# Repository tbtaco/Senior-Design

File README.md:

The Senior Design project I was able to be a part of in Fall 2019 and Spring 2020 at K-State was the "MAC Address Finder".  For that, I worked in a group of 4 to fully design and build our device.  My role was mainly designing the circuit and building the board containing the microcontroller, and the board with the Wi-Fi module.  The device is needed in the residence halls for IT staff to quickly get certain device's MAC addresses.  The main reason for needing this device is the Google Home Mini.  They normally don't have a printed MAC address on the outside of the product and must be connected to a network to retrieve the address.  Our device creates that network to connect to and gives a very easy way to see this address.  The MAC address can then be used to manually add the device to the university network.

Schematics and board layouts can be found in the [EAGLE](https://github.com/tbtaco/Senior-Design/tree/main/EAGLE) directory.  The 3 main folders in there represent the separate orders I placed.  The final versions of each board I designed are:

[Main Board](https://github.com/tbtaco/Senior-Design/tree/main/EAGLE/Batch%201/Main%20Board) - This was the first version of the main PCB and I intended on redoing it at some point but it never happened due to budget constraints, time constraints, and Covid-19's impact on everything.
    
[Wifi Board](https://github.com/tbtaco/Senior-Design/tree/main/EAGLE/Batch%203/Wifi%20Board%20Rework) - I had the Wi-Fi portion working on a breadboard for the most part and turned that into a PCB.  There were some inconsistencies with different online documentation that messed up a couple things with my first version of the Wi-Fi board PCB.  We didn't have time for several attempts so I designed some breakout boards to test things before ordering the final version of this board.  The final version has several switches for debugging just in case things went horribly wrong which could easily be removed if another version were possibe.
    
[Button Board](https://github.com/tbtaco/Senior-Design/tree/main/EAGLE/Batch%201/Button%20Board) - A rather simple board that has an RGB LED and 3 buttons for input.
    
[Programmer Board](https://github.com/tbtaco/Senior-Design/tree/main/EAGLE/Batch%202/Programmer%20Board) - After several redesigns, this is the final board I created to assist with programming the microcontroller and Wi-Fi module.  It fits on top of an Arduino Uno for programming the microcontroller, and on top of a Metro M4 Express for programming the Wi-Fi module.

I also wrote the code to go on the microcontroller.  I hadn't intended on writing the final code for this project but it sort of just happened as I needed it for testing and we were short on time toward the end of semester.  This Arduino file along with the two edited programs for programming the boards can be found in the [Arduino](https://github.com/tbtaco/Senior-Design/tree/main/Arduino) directory.

I have some additional pictures and screenshots that don't fit in one of the two categories above, so I put them in the [Other Resources](https://github.com/tbtaco/Senior-Design/tree/main/Other%20Resources) directory.

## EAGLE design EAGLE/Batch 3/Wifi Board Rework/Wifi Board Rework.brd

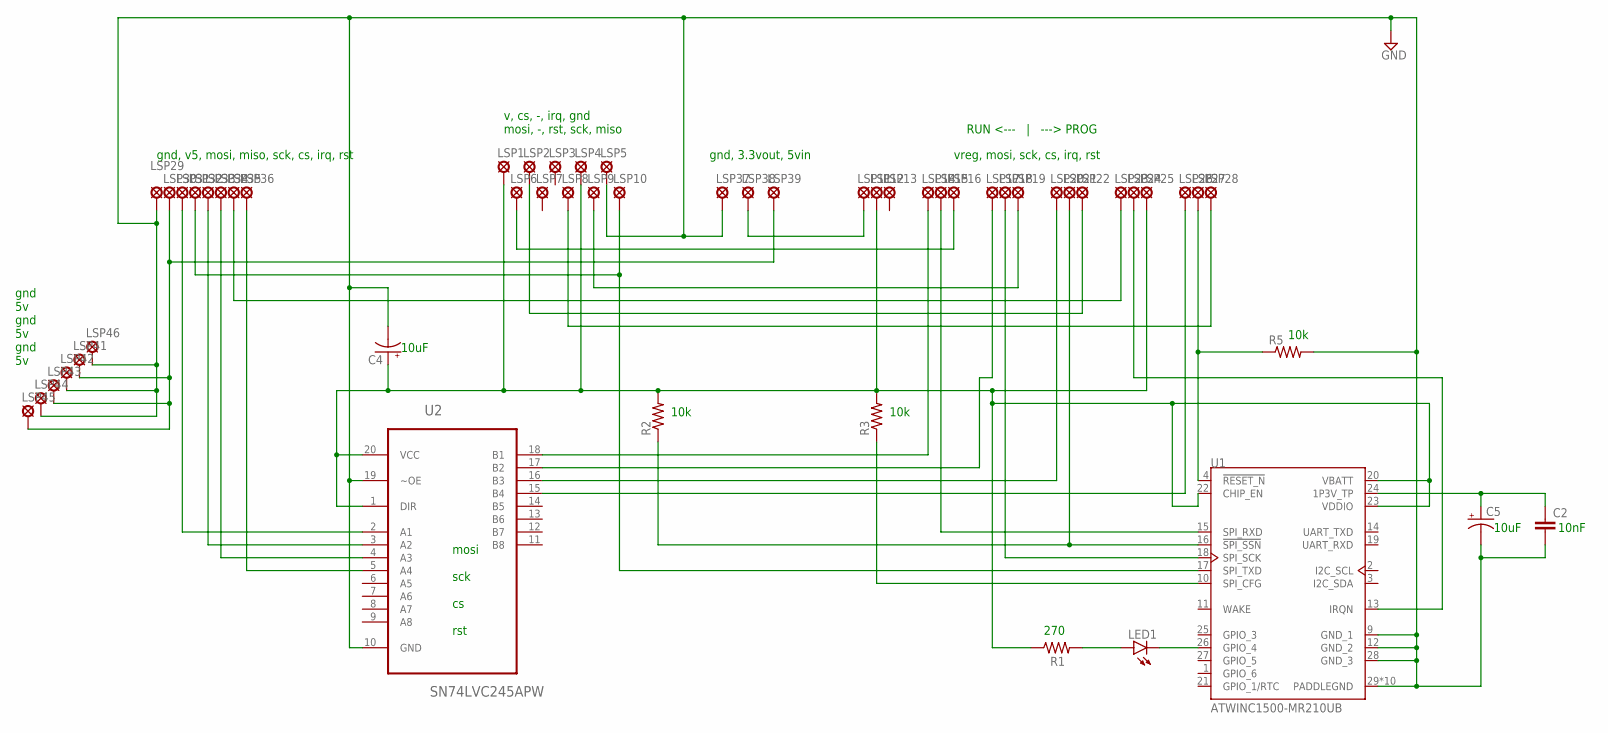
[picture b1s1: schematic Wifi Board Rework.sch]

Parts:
C2: C5/2.5; C5B2.5
C4, C5: CPOL-USE2-4; E2-4
LED1: LED5MM
LSP1, LSP2, LSP3, LSP4, LSP5, LSP7, LSP8, LSP9, LSP10, LSP11, LSP12, LSP13, LSP14, LSP15, LSP16, LSP17, LSP18, LSP19, LSP20, LSP21, LSP22, LSP23, LSP24, LSP25, LSP26, LSP27, LSP28, LSP30, LSP31, LSP32, LSP33, LSP34, LSP35, LSP36, LSP38, LSP39, LSP41, LSP42, LSP43, LSP44, LSP45: LSP10_CLSP10_C; LSP10_C
LSP6, LSP29, LSP37, LSP46: LSP10_S
R1, R2, R3, R5: R-US_VMTA55; VMTA55
U1: ATWINC1500-MR210UB; MICROCHIP_ATWINC1500-MR210UB
U2: SN74LVC245APW; SOP65P640X120-20N

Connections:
GND: C2.2, C4.-, C5.-, LSP5.P$1, LSP29.P$1, LSP37.P$1, LSP42.P$1, LSP44.P$1, LSP46.P$1, R5.2, U1.9 (GND_1), U1.12 (GND_2), U1.28 (GND_3), U1.29 (PADDLEGND), U1.P$1 (PADDLEGND), U1.P$2 (PADDLEGND), U1.P$3 (PADDLEGND), U1.P$4 (PADDLEGND), U1.P$5 (PADDLEGND), U1.P$6 (PADDLEGND), U1.P$7 (PADDLEGND), U1.P$8 (PADDLEGND), U1.P$9 (PADDLEGND), U2.10 (GND), U2.19 (~OE)
unnamed: LED1.K (C), U1.26 (GPIO_4)
unnamed: LED1.A, R1.2
unnamed: C4.+, LSP1.P$1, LSP4.P$1, LSP12.P$1, LSP25.P$1, R1.1, R2.2, R3.2, U1.20 (VBATT), U1.22 (CHIP_EN), U1.23 (VDDIO), U2.1 (DIR), U2.20 (VCC)
unnamed: LSP11.P$1, LSP38.P$1
unnamed: R3.1, U1.10 (SPI_CFG)
unnamed: LSP10.P$1, LSP32.P$1, U1.17 (SPI_TXD)
unnamed: LSP30.P$1, LSP39.P$1, LSP41.P$1, LSP43.P$1, LSP45.P$1
unnamed: LSP23.P$1, LSP35.P$1
unnamed: LSP15.P$1, U1.15 (SPI_RXD)
unnamed: LSP6.P$1, LSP16.P$1
unnamed: LSP9.P$1, LSP19.P$1
unnamed: LSP2.P$1, LSP22.P$1
unnamed: LSP24.P$1, U1.13 (IRQN)
unnamed: C2.1, C5.+, U1.24 (1P3V_TP)
unnamed: LSP14.P$1, U2.18 (B1)
unnamed: LSP17.P$1, U2.17 (B2)
unnamed: LSP20.P$1, U2.16 (B3)
unnamed: LSP26.P$1, U2.15 (B4)
unnamed: LSP27.P$1, R5.1, U1.4 (!RESET_N)
unnamed: LSP34.P$1, U2.4 (A3)
unnamed: LSP18.P$1, U1.18 (SPI_SCK)
unnamed: LSP21.P$1, R2.1, U1.16 (!SPI_SSN)
unnamed: LSP36.P$1, U2.5 (A4)
unnamed: LSP33.P$1, U2.3 (A2)
unnamed: LSP31.P$1, U2.2 (A1)
unnamed: LSP8.P$1, LSP28.P$1

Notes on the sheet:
v, cs, -, irq, gnd mosi, -, rst, sck, miso
vreg, mosi, sck, cs, irq, rst
gnd, v5, mosi, miso, sck, cs, irq, rst
10k
10uF
10nF
270
gnd, 3.3vout, 5vin
RUN <--- | ---> PROG
gnd 5v gnd 5v gnd 5v
mosi sck cs rst

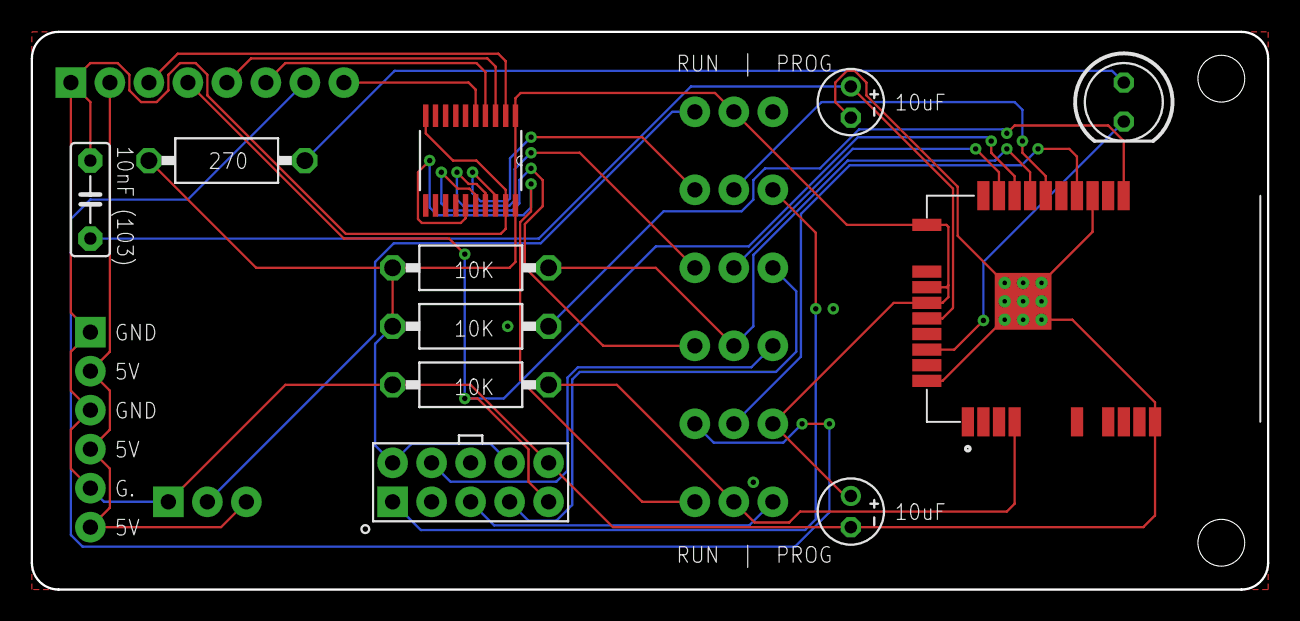
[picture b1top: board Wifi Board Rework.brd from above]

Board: 2 copper layers, 80.5 x 36.3 mm, 55 parts (0 on the bottom side), 27 nets.

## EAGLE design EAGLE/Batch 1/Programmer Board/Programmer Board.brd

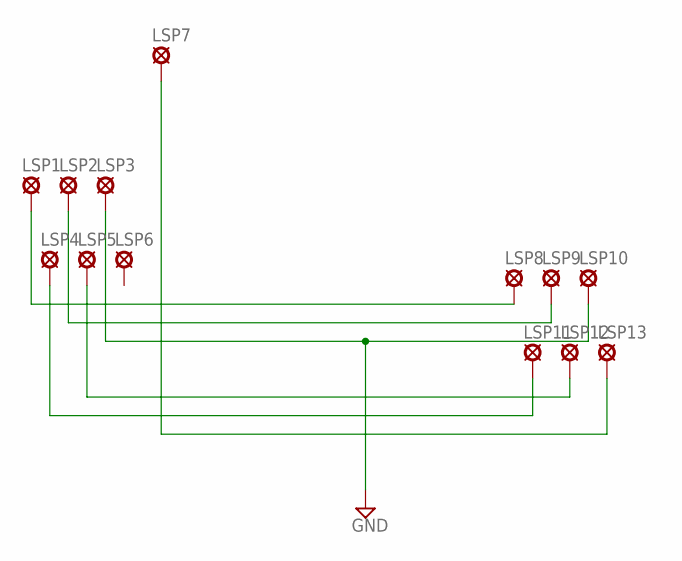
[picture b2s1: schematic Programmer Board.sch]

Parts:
LSP1, LSP2, LSP3, LSP4, LSP5, LSP6, LSP7, LSP8, LSP9, LSP10, LSP11, LSP12, LSP13: LSP10_CLSP10_C; LSP10_C

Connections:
GND: LSP3.P$1, LSP10.P$1
unnamed: LSP1.P$1, LSP8.P$1
unnamed: LSP2.P$1, LSP9.P$1
unnamed: LSP4.P$1, LSP11.P$1
unnamed: LSP5.P$1, LSP12.P$1
unnamed: LSP7.P$1, LSP13.P$1

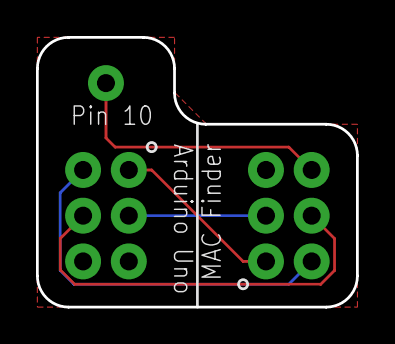
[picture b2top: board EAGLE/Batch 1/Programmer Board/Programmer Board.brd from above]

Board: 2 copper layers, 17.8 x 15.0 mm, 13 parts (0 on the bottom side), 6 nets.

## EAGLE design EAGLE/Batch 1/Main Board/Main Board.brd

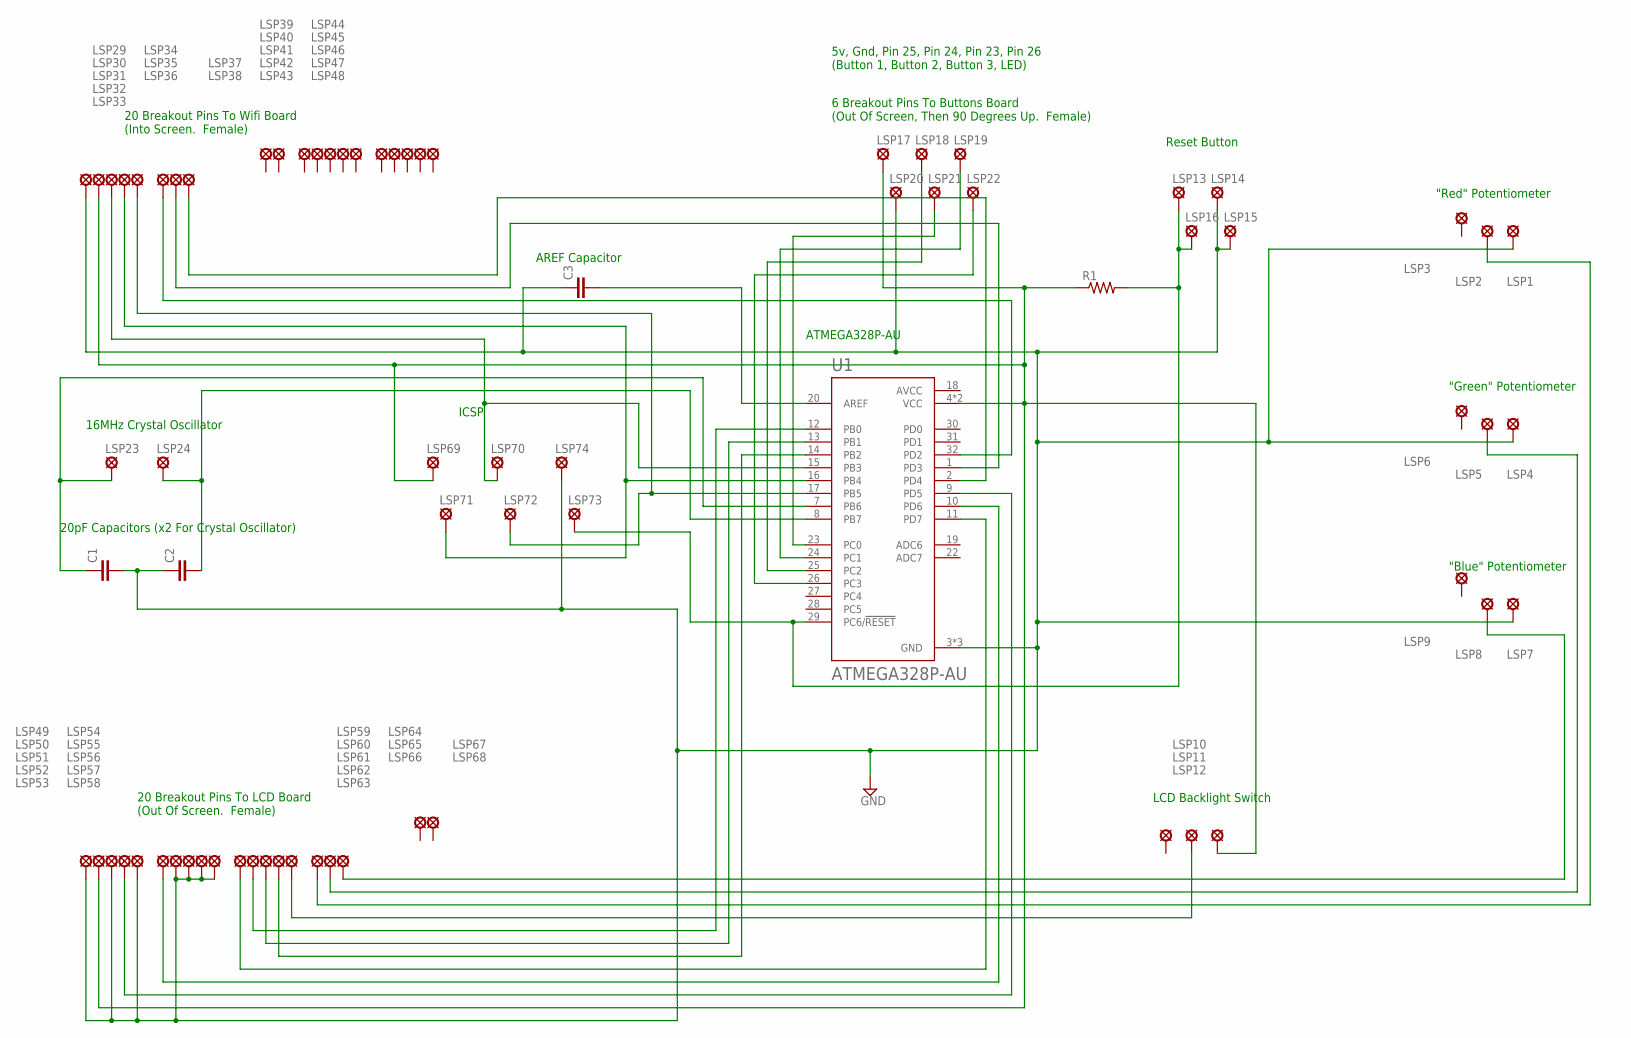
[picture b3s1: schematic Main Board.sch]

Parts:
C1, C2, C3: C5/2.5; C5B2.5
LSP1, LSP2, LSP3, LSP4, LSP5, LSP6, LSP7, LSP8, LSP9, LSP10, LSP11, LSP12, LSP13, LSP14, LSP15, LSP16, LSP17, LSP18, LSP19, LSP20, LSP21, LSP22, LSP23, LSP24, LSP29, LSP30, LSP31, LSP32, LSP33, LSP34, LSP35, LSP36, LSP37, LSP38, LSP39, LSP40, LSP41, LSP42, LSP43, LSP44, LSP45, LSP46, LSP47, LSP48, LSP49, LSP50, LSP51, LSP52, LSP53, LSP54, LSP55, LSP56, LSP57, LSP58, LSP59, LSP60, LSP61, LSP62, LSP63, LSP64, LSP65, LSP66, LSP67, LSP68, LSP69, LSP70, LSP71, LSP72, LSP73, LSP74: LSP10_CLSP10_C; LSP10_C
R1: R-US_VMTA55; VMTA55
U1: ATMEGA328P-AU; QFP80P900X900X120-32N

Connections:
AVCC: U1.18 (AVCC)
GND: C1.2, C2.1, C3.1, LSP1.P$1, LSP4.P$1, LSP7.P$1, LSP14.P$1, LSP15.P$1, LSP20.P$1, LSP29.P$1, LSP49.P$1, LSP51.P$1, LSP53.P$1, LSP55.P$1, LSP56.P$1, LSP57.P$1, LSP58.P$1, LSP74.P$1, U1.3 (GND), U1.5 (GND), U1.21 (GND)
unnamed: LSP2.P$1, LSP64.P$1
unnamed: LSP31.P$1, LSP70.P$1, U1.15 (PB3)
unnamed: LSP5.P$1, LSP65.P$1
unnamed: C1.1, LSP23.P$1, U1.7 (PB6)
unnamed: C2.2, LSP24.P$1, U1.8 (PB7)
unnamed: LSP8.P$1, LSP66.P$1
unnamed: LSP33.P$1, LSP72.P$1, U1.17 (PB5)
unnamed: LSP32.P$1, LSP71.P$1, U1.16 (PB4)
unnamed: LSP13.P$1, LSP16.P$1, LSP73.P$1, R1.2, U1.29 (PC6/!RESET)
unnamed: LSP22.P$1, U1.26 (PC3)
unnamed: LSP18.P$1, U1.25 (PC2)
unnamed: LSP19.P$1, U1.24 (PC1)
unnamed: LSP52.P$1, U1.9 (PD5)
unnamed: LSP54.P$1, U1.10 (PD6)
unnamed: LSP59.P$1, U1.11 (PD7)
unnamed: LSP60.P$1, U1.12 (PB0)
unnamed: LSP61.P$1, U1.13 (PB1)
unnamed: LSP62.P$1, U1.14 (PB2)
unnamed: LSP11.P$1, LSP63.P$1
unnamed: LSP12.P$1, LSP17.P$1, LSP30.P$1, LSP50.P$1, LSP69.P$1, R1.1, U1.4 (VCC), U1.6 (VCC)
unnamed: LSP21.P$1, U1.23 (PC0)
unnamed: C3.2, U1.20 (AREF)
unnamed: LSP34.P$1, U1.32 (PD2)
unnamed: LSP35.P$1, U1.1 (PD3)
unnamed: LSP36.P$1, U1.2 (PD4)

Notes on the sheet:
ICSP
ATMEGA328P-AU
6 Breakout Pins To Buttons Board (Out Of Screen, Then 90 Degrees Up. Female)
20 Breakout Pins To Wifi Board (Into Screen. Female)
20 Breakout Pins To LCD Board (Out Of Screen. Female)
16MHz Crystal Oscillator
20pF Capacitors (x2 For Crystal Oscillator)
Reset Button
"Red" Potentiometer
"Green" Potentiometer
"Blue" Potentiometer
LCD Backlight Switch
AREF Capacitor
5v, Gnd, Pin 25, Pin 24, Pin 23, Pin 26 (Button 1, Button 2, Button 3, LED)

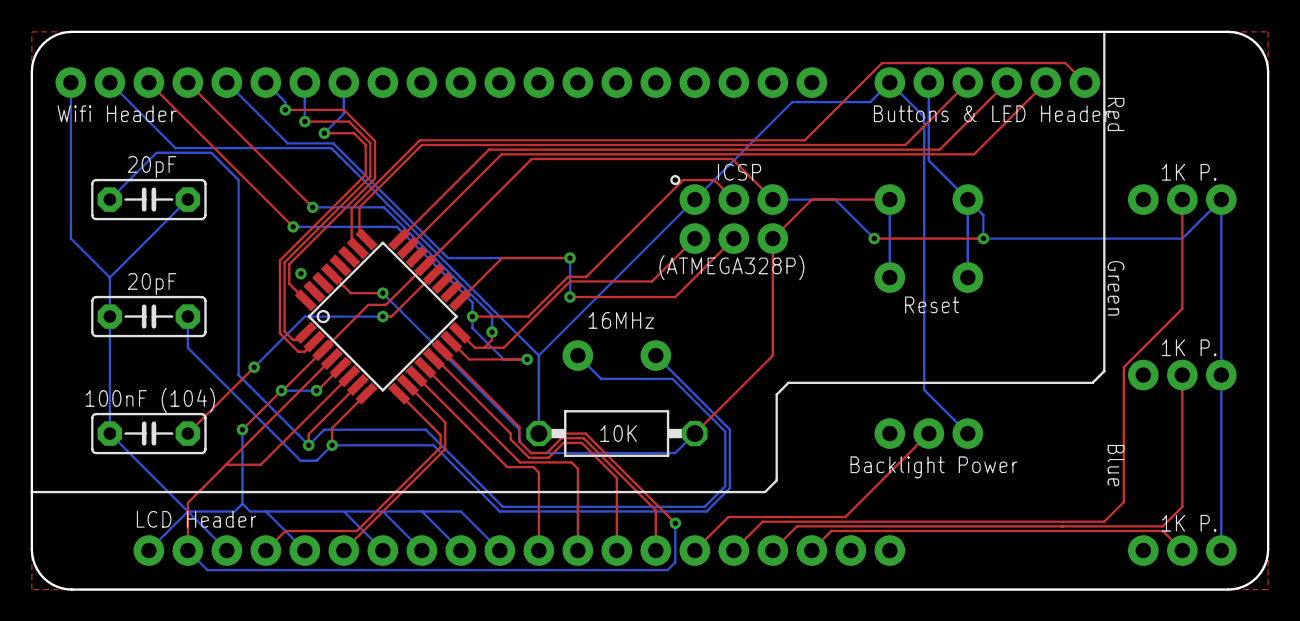
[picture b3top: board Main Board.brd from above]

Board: 2 copper layers, 80.5 x 36.3 mm, 75 parts (0 on the bottom side), 26 nets.

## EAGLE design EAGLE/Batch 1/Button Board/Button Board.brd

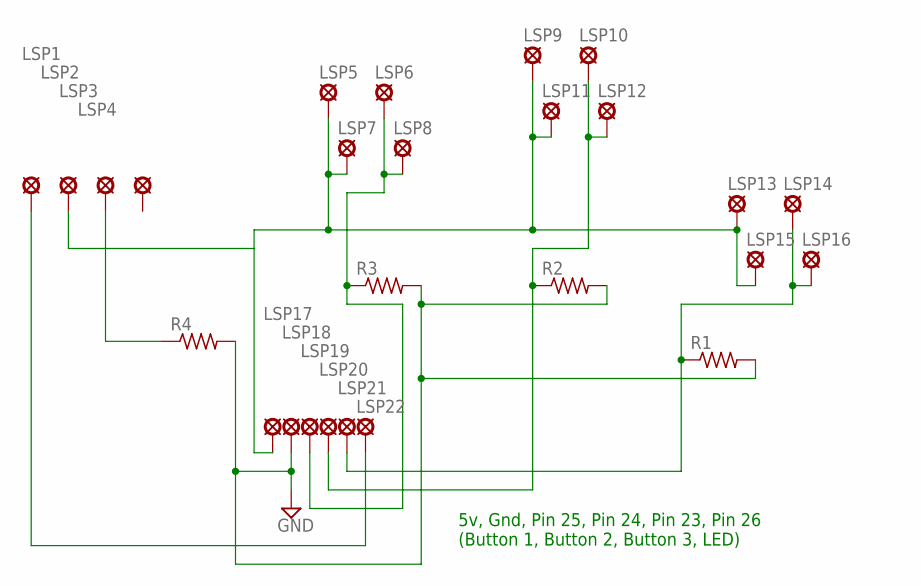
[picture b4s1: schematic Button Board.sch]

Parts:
LSP1, LSP2, LSP3, LSP4, LSP5, LSP6, LSP7, LSP8, LSP9, LSP10, LSP11, LSP12, LSP13, LSP14, LSP15, LSP16, LSP17, LSP18, LSP19, LSP20, LSP21, LSP22: LSP10_CLSP10_C; LSP10_C
R1, R2, R3, R4: R-US_VMTA55; VMTA55

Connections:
GND: LSP18.P$1, R1.2, R2.2, R3.2, R4.2
unnamed: LSP6.P$1, LSP8.P$1, LSP19.P$1, R3.1
unnamed: LSP3.P$1, R4.1
unnamed: LSP10.P$1, LSP12.P$1, LSP20.P$1, R2.1
unnamed: LSP2.P$1, LSP5.P$1, LSP7.P$1, LSP9.P$1, LSP11.P$1, LSP13.P$1, LSP15.P$1, LSP17.P$1
unnamed: LSP14.P$1, LSP16.P$1, LSP21.P$1, R1.1
unnamed: LSP1.P$1, LSP22.P$1

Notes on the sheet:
5v, Gnd, Pin 25, Pin 24, Pin 23, Pin 26 (Button 1, Button 2, Button 3, LED)

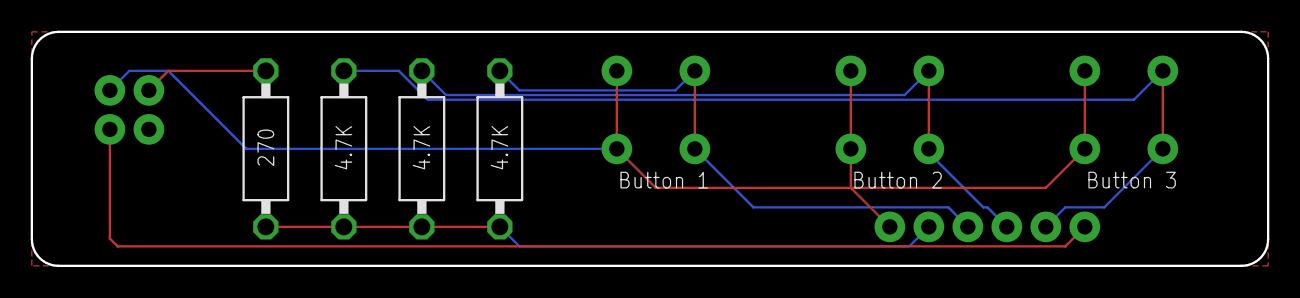
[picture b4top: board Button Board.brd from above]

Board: 2 copper layers, 80.5 x 15.2 mm, 26 parts (0 on the bottom side), 7 nets.

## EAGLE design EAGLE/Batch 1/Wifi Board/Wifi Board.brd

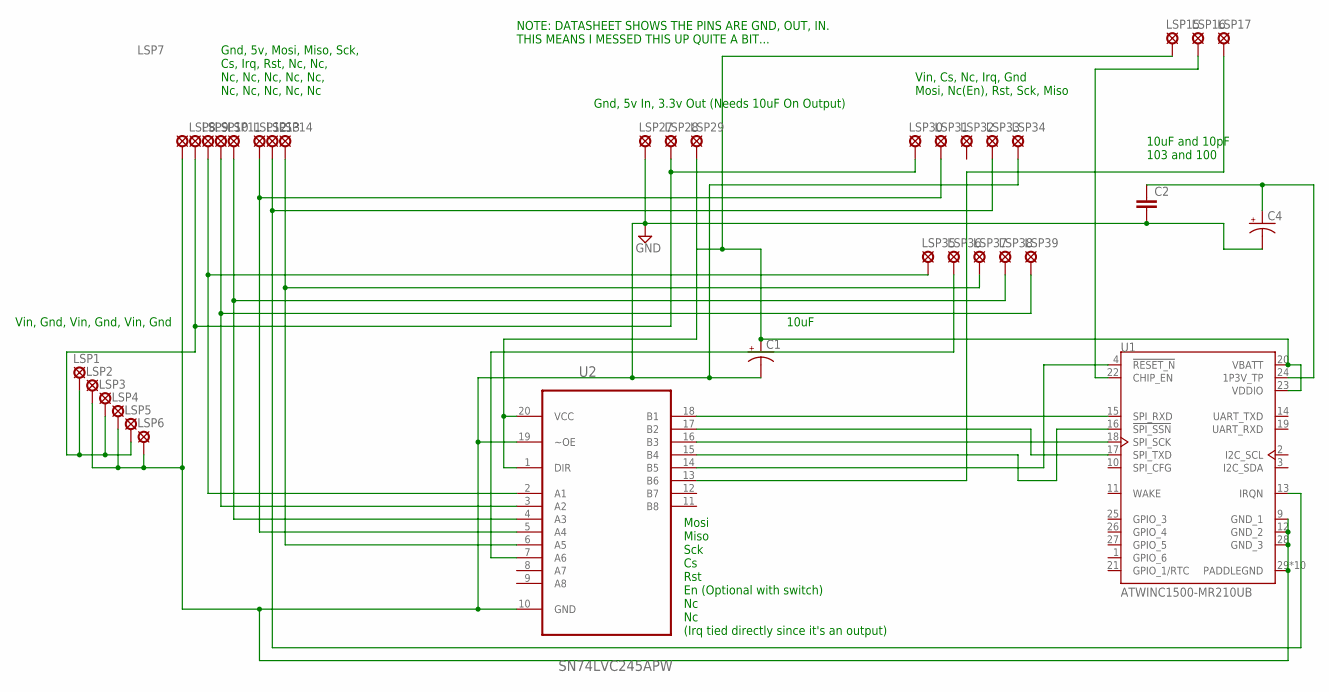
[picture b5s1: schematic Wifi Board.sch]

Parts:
C1, C4: CPOL-USE2-4; E2-4
C2: C5/2.5; C5B2.5
LSP1, LSP2, LSP3, LSP4, LSP5, LSP6, LSP7, LSP8, LSP9, LSP10, LSP11, LSP12, LSP13, LSP14, LSP15, LSP16, LSP17, LSP27, LSP28, LSP29, LSP30, LSP31, LSP32, LSP33, LSP34, LSP35, LSP36, LSP37, LSP38, LSP39: LSP10_CLSP10_C; LSP10_C
U1: ATWINC1500-MR210UB; MICROCHIP_ATWINC1500-MR210UB
U2: SN74LVC245APW; SOP65P640X120-20N

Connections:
GND: C1.-, C2.2, C4.-, LSP2.P$1, LSP4.P$1, LSP6.P$1, LSP7.P$1, LSP27.P$1, LSP34.P$1, U1.9 (GND_1), U1.12 (GND_2), U1.28 (GND_3), U1.29 (PADDLEGND), U1.P$1 (PADDLEGND), U1.P$2 (PADDLEGND), U1.P$3 (PADDLEGND), U1.P$4 (PADDLEGND), U1.P$5 (PADDLEGND), U1.P$6 (PADDLEGND), U1.P$7 (PADDLEGND), U1.P$8 (PADDLEGND), U1.P$9 (PADDLEGND), U2.10 (GND), U2.19 (~OE)
unnamed: LSP36.P$1, U2.7 (A6)
unnamed: LSP1.P$1, LSP3.P$1, LSP5.P$1, LSP8.P$1, LSP28.P$1, LSP30.P$1
unnamed: C1.+, LSP15.P$1, LSP29.P$1, U1.20 (VBATT), U1.23 (VDDIO), U2.1 (DIR), U2.20 (VCC)
unnamed: LSP9.P$1, LSP35.P$1, U2.2 (A1)
unnamed: LSP10.P$1, LSP39.P$1, U2.3 (A2)
unnamed: LSP11.P$1, LSP38.P$1, U2.4 (A3)
unnamed: LSP12.P$1, LSP31.P$1, U2.5 (A4)
unnamed: LSP13.P$1, LSP33.P$1, U1.13 (IRQN)
unnamed: LSP14.P$1, LSP37.P$1, U2.6 (A5)
unnamed: U1.15 (SPI_RXD), U2.18 (B1)
unnamed: U1.17 (SPI_TXD), U2.17 (B2)
unnamed: U1.18 (SPI_SCK), U2.16 (B3)
unnamed: U1.16 (!SPI_SSN), U2.15 (B4)
unnamed: LSP17.P$1, U2.13 (B6)
unnamed: U1.4 (!RESET_N), U2.14 (B5)
unnamed: LSP16.P$1, U1.22 (CHIP_EN)
unnamed: C2.1, C4.+, U1.24 (1P3V_TP)

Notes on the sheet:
Gnd, 5v, Mosi, Miso, Sck, Cs, Irq, Rst, Nc, Nc, Nc, Nc, Nc, Nc, Nc, Nc, Nc, Nc, Nc, Nc
Gnd, 5v In, 3.3v Out (Needs 10uF On Output)
Vin, Cs, Nc, Irq, Gnd Mosi, Nc(En), Rst, Sck, Miso
Vin, Gnd, Vin, Gnd, Vin, Gnd
10uF
Mosi Miso Sck Cs Rst En (Optional with switch) Nc Nc (Irq tied directly since it's an output)
10uF and 10pF 103 and 100
NOTE: DATASHEET SHOWS THE PINS ARE GND, OUT, IN. THIS MEANS I MESSED THIS UP QUITE A BIT...

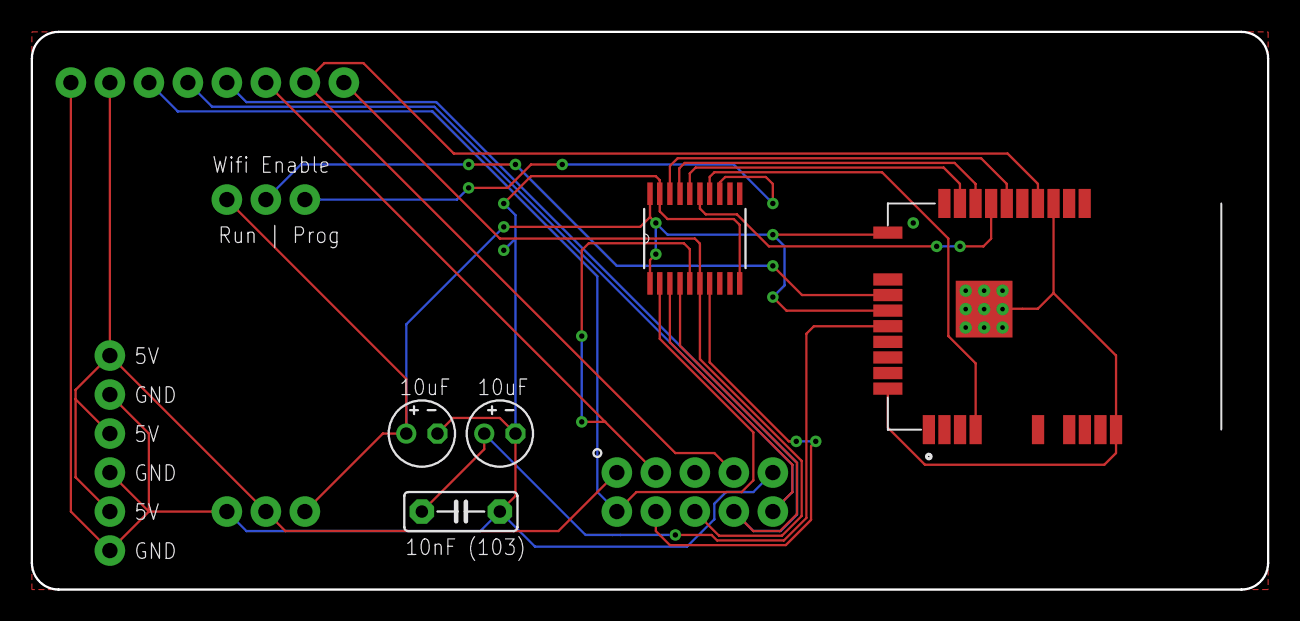
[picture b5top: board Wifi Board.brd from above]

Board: 2 copper layers, 80.5 x 36.3 mm, 35 parts (0 on the bottom side), 18 nets.

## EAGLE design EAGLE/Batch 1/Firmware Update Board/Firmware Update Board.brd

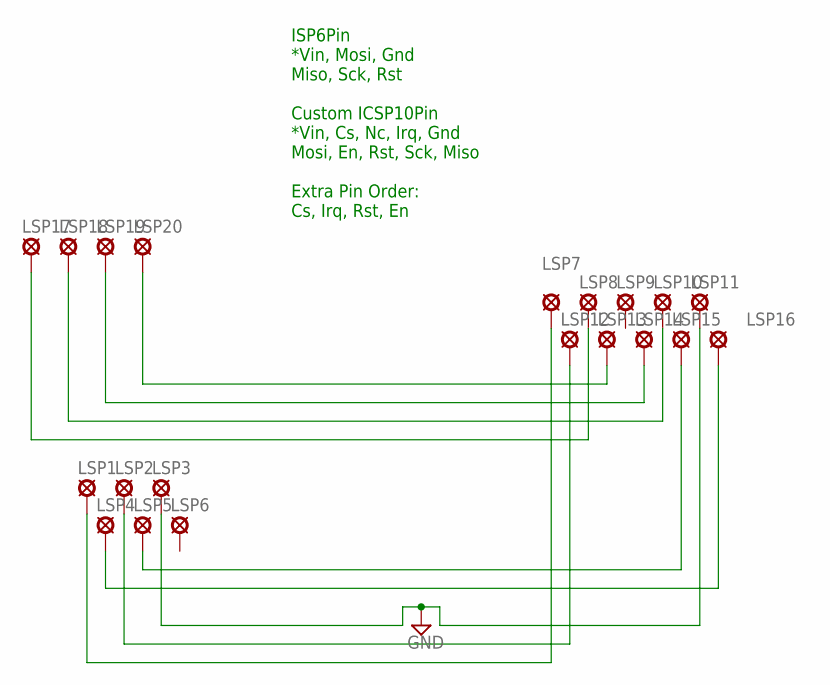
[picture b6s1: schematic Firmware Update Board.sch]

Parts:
LSP1, LSP2, LSP3, LSP4, LSP5, LSP6, LSP7, LSP8, LSP9, LSP10, LSP11, LSP12, LSP13, LSP14, LSP15, LSP16, LSP17, LSP18, LSP19, LSP20: LSP10_CLSP10_C; LSP10_C

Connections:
GND: LSP3.P$1, LSP11.P$1
unnamed: LSP1.P$1, LSP7.P$1
unnamed: LSP2.P$1, LSP12.P$1
unnamed: LSP4.P$1, LSP16.P$1
unnamed: LSP5.P$1, LSP15.P$1
unnamed: LSP13.P$1, LSP20.P$1
unnamed: LSP14.P$1, LSP19.P$1
unnamed: LSP10.P$1, LSP18.P$1
unnamed: LSP8.P$1, LSP17.P$1

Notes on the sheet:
ISP6Pin *Vin, Mosi, Gnd Miso, Sck, Rst Custom ICSP10Pin *Vin, Cs, Nc, Irq, Gnd Mosi, En, Rst, Sck, Miso Extra Pin Order: Cs, Irq, Rst, En

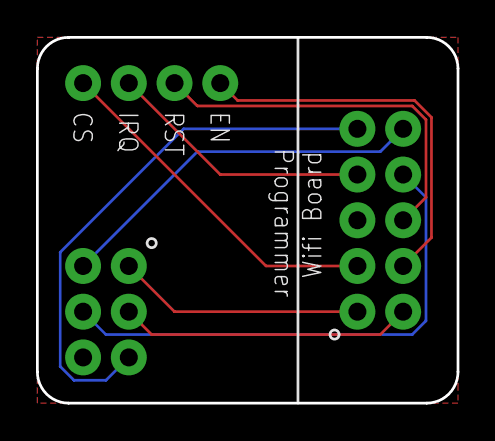
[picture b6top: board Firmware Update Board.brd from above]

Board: 2 copper layers, 23.4 x 20.3 mm, 20 parts (0 on the bottom side), 9 nets.

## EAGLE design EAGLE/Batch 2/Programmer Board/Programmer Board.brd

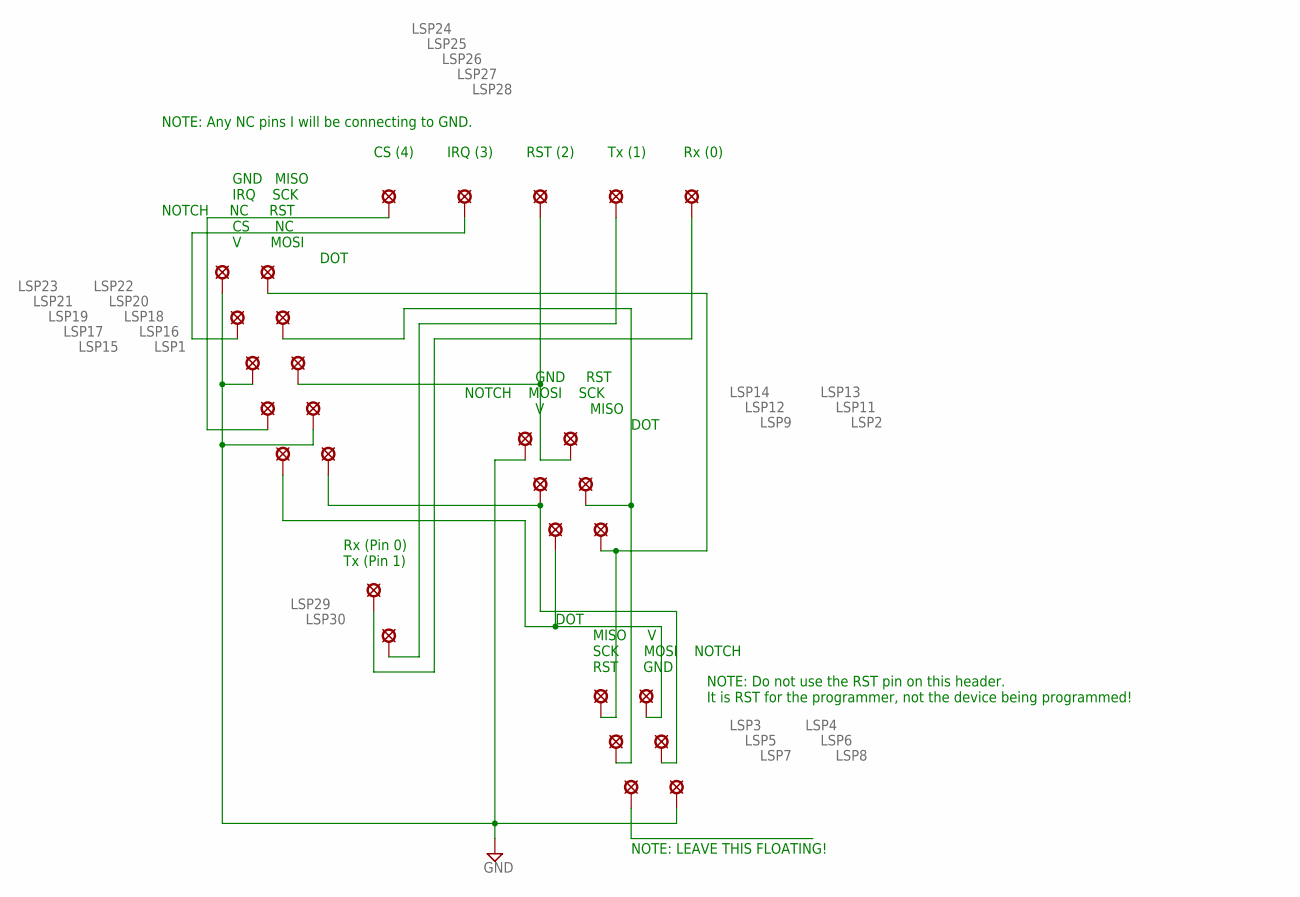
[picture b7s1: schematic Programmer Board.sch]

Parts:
LSP1, LSP2, LSP3, LSP28, LSP29: LSP10_S
LSP4, LSP5, LSP6, LSP7, LSP8, LSP9, LSP11, LSP12, LSP13, LSP14, LSP15, LSP16, LSP17, LSP18, LSP19, LSP20, LSP21, LSP22, LSP23, LSP24, LSP25, LSP26, LSP27, LSP30: LSP10_CLSP10_C; LSP10_C

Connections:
GND: LSP8.P$1, LSP14.P$1, LSP16.P$1, LSP19.P$1, LSP23.P$1
unnamed: LSP5.P$1, LSP11.P$1, LSP20.P$1
unnamed: LSP27.P$1, LSP30.P$1
unnamed: LSP28.P$1, LSP29.P$1
unnamed: LSP1.P$1, LSP6.P$1, LSP12.P$1
unnamed: LSP2.P$1, LSP3.P$1, LSP22.P$1
unnamed: LSP4.P$1, LSP9.P$1, LSP15.P$1
unnamed: LSP17.P$1, LSP24.P$1
unnamed: LSP21.P$1, LSP25.P$1
unnamed: LSP13.P$1, LSP18.P$1, LSP26.P$1

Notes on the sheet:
GND MISO IRQ SCK NOTCH NC RST CS NC V MOSI DOT
GND RST NOTCH MOSI SCK V MISO DOT
Rx (Pin 0) Tx (Pin 1)
CS (4) IRQ (3) RST (2) Tx (1) Rx (0)
DOT MISO V SCK MOSI NOTCH RST GND
NOTE: Do not use the RST pin on this header. It is RST for the programmer, not the device being programmed!
NOTE: Any NC pins I will be connecting to GND.
NOTE: LEAVE THIS FLOATING!

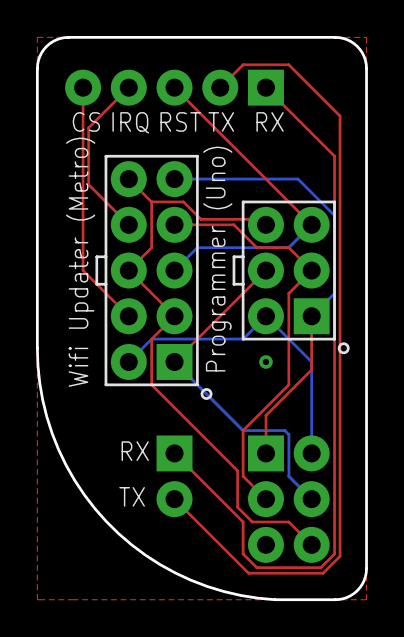
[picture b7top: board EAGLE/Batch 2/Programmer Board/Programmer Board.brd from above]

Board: 2 copper layers, 18.3 x 31.2 mm, 29 parts (0 on the bottom side), 10 nets.
